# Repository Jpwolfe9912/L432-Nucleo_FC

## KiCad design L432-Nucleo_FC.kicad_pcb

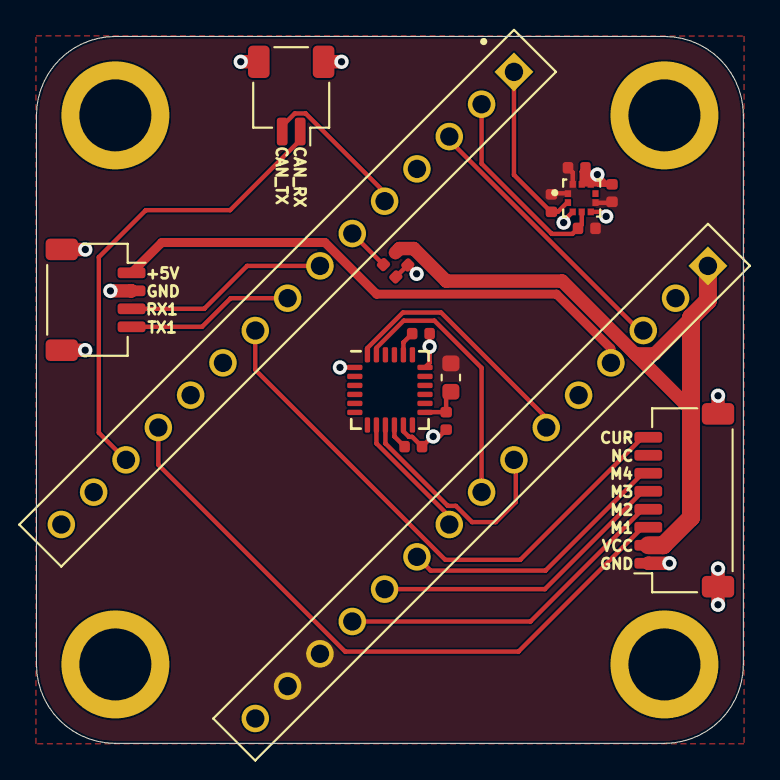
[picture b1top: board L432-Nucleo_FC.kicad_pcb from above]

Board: 2 copper layers, 39.3 x 39.3 mm, 20 parts (0 on the bottom side), 24 nets.

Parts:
C1, C3, C4, C5: 0.1uF; C_0402_1005Metric
C2: 2.2uF; C_0402_1005Metric
FB1: 100@100MHz; L_0603_1608Metric
H1, H2, H3, H4: MountingHole_Pad; MountingHole_2.7mm_Pad
J1: Conn_01x04; JST_SH_SM04B-SRSS-TB_1x04-1MP_P1.00mm_Horizontal
J2: Conn_01x08; JST_SH_SM08B-SRSS-TB_1x08-1MP_P1.00mm_Horizontal
J3: Conn_01x03; JST_SH_SM02B-SRSS-TB_1x02-1MP_P1.00mm_Horizontal
R1, R2: 4.7k; R_0402_1005Metric
R3: 10k; R_0402_1005Metric
R4: 1k; R_0402_1005Metric
U1: MPU-6000; InvenSense_QFN-24_4x4mm_P0.5mm
U2: NUCLEO32-L432KC; MODULE_NUCLEO-L432KC
U3: BMP388

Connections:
+3V3: C4.1, C5.1, FB1.2, R1.2, R2.2, U2.28, U2.29, U3.1, U3.6, U3.10
+3V3_GYRO: C1.1, FB1.1, U1.13
+5V: J1.1, U2.19
/Connectors/CAN1_RX: J3.1, U2.13
/Connectors/CAN1_TX: J3.2, U2.5
/Connectors/CURR: J2.8, U2.9
/Connectors/M1: J2.3, U2.12
/Connectors/M2: J2.4, U2.27
/Connectors/M3: J2.5, U2.26
/Connectors/M4: J2.6, U2.25
/Connectors/USART1_RX: J1.3, U2.7
/Connectors/USART1_TX: J1.4, U2.8
/Gyro/SPI1_CS: U1.8, U2.24
/Gyro/SPI1_MISO: U1.9, U2.22
/Gyro/SPI1_MOSI: U1.24, U2.21
/Gyro/SPI1_SCK: U1.23, U2.23
/Nucleo/I2C1_SCL: R1.1, U2.1, U3.2
/Nucleo/I2C1_SDA: R2.1, U2.2, U3.4
/Nucleo/SENSE: R4.1, U2.6
GND: C1.2, C2.2, C3.2, C4.2, C5.2, H1.1, H2.1, H3.1, H4.1, J1.2, J2.1, J3.3, R3.2, R4.2, U1.1, U1.11, U1.18, U2.4, U2.17, U3.3, U3.5, U3.8, U3.9
unnamed: C2.1, U1.20
unnamed: C3.1, U1.10
unnamed: U2.3, U2.18
VCC: J2.2, R3.1, U2.16

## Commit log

2021-04-30 Added all files for project
